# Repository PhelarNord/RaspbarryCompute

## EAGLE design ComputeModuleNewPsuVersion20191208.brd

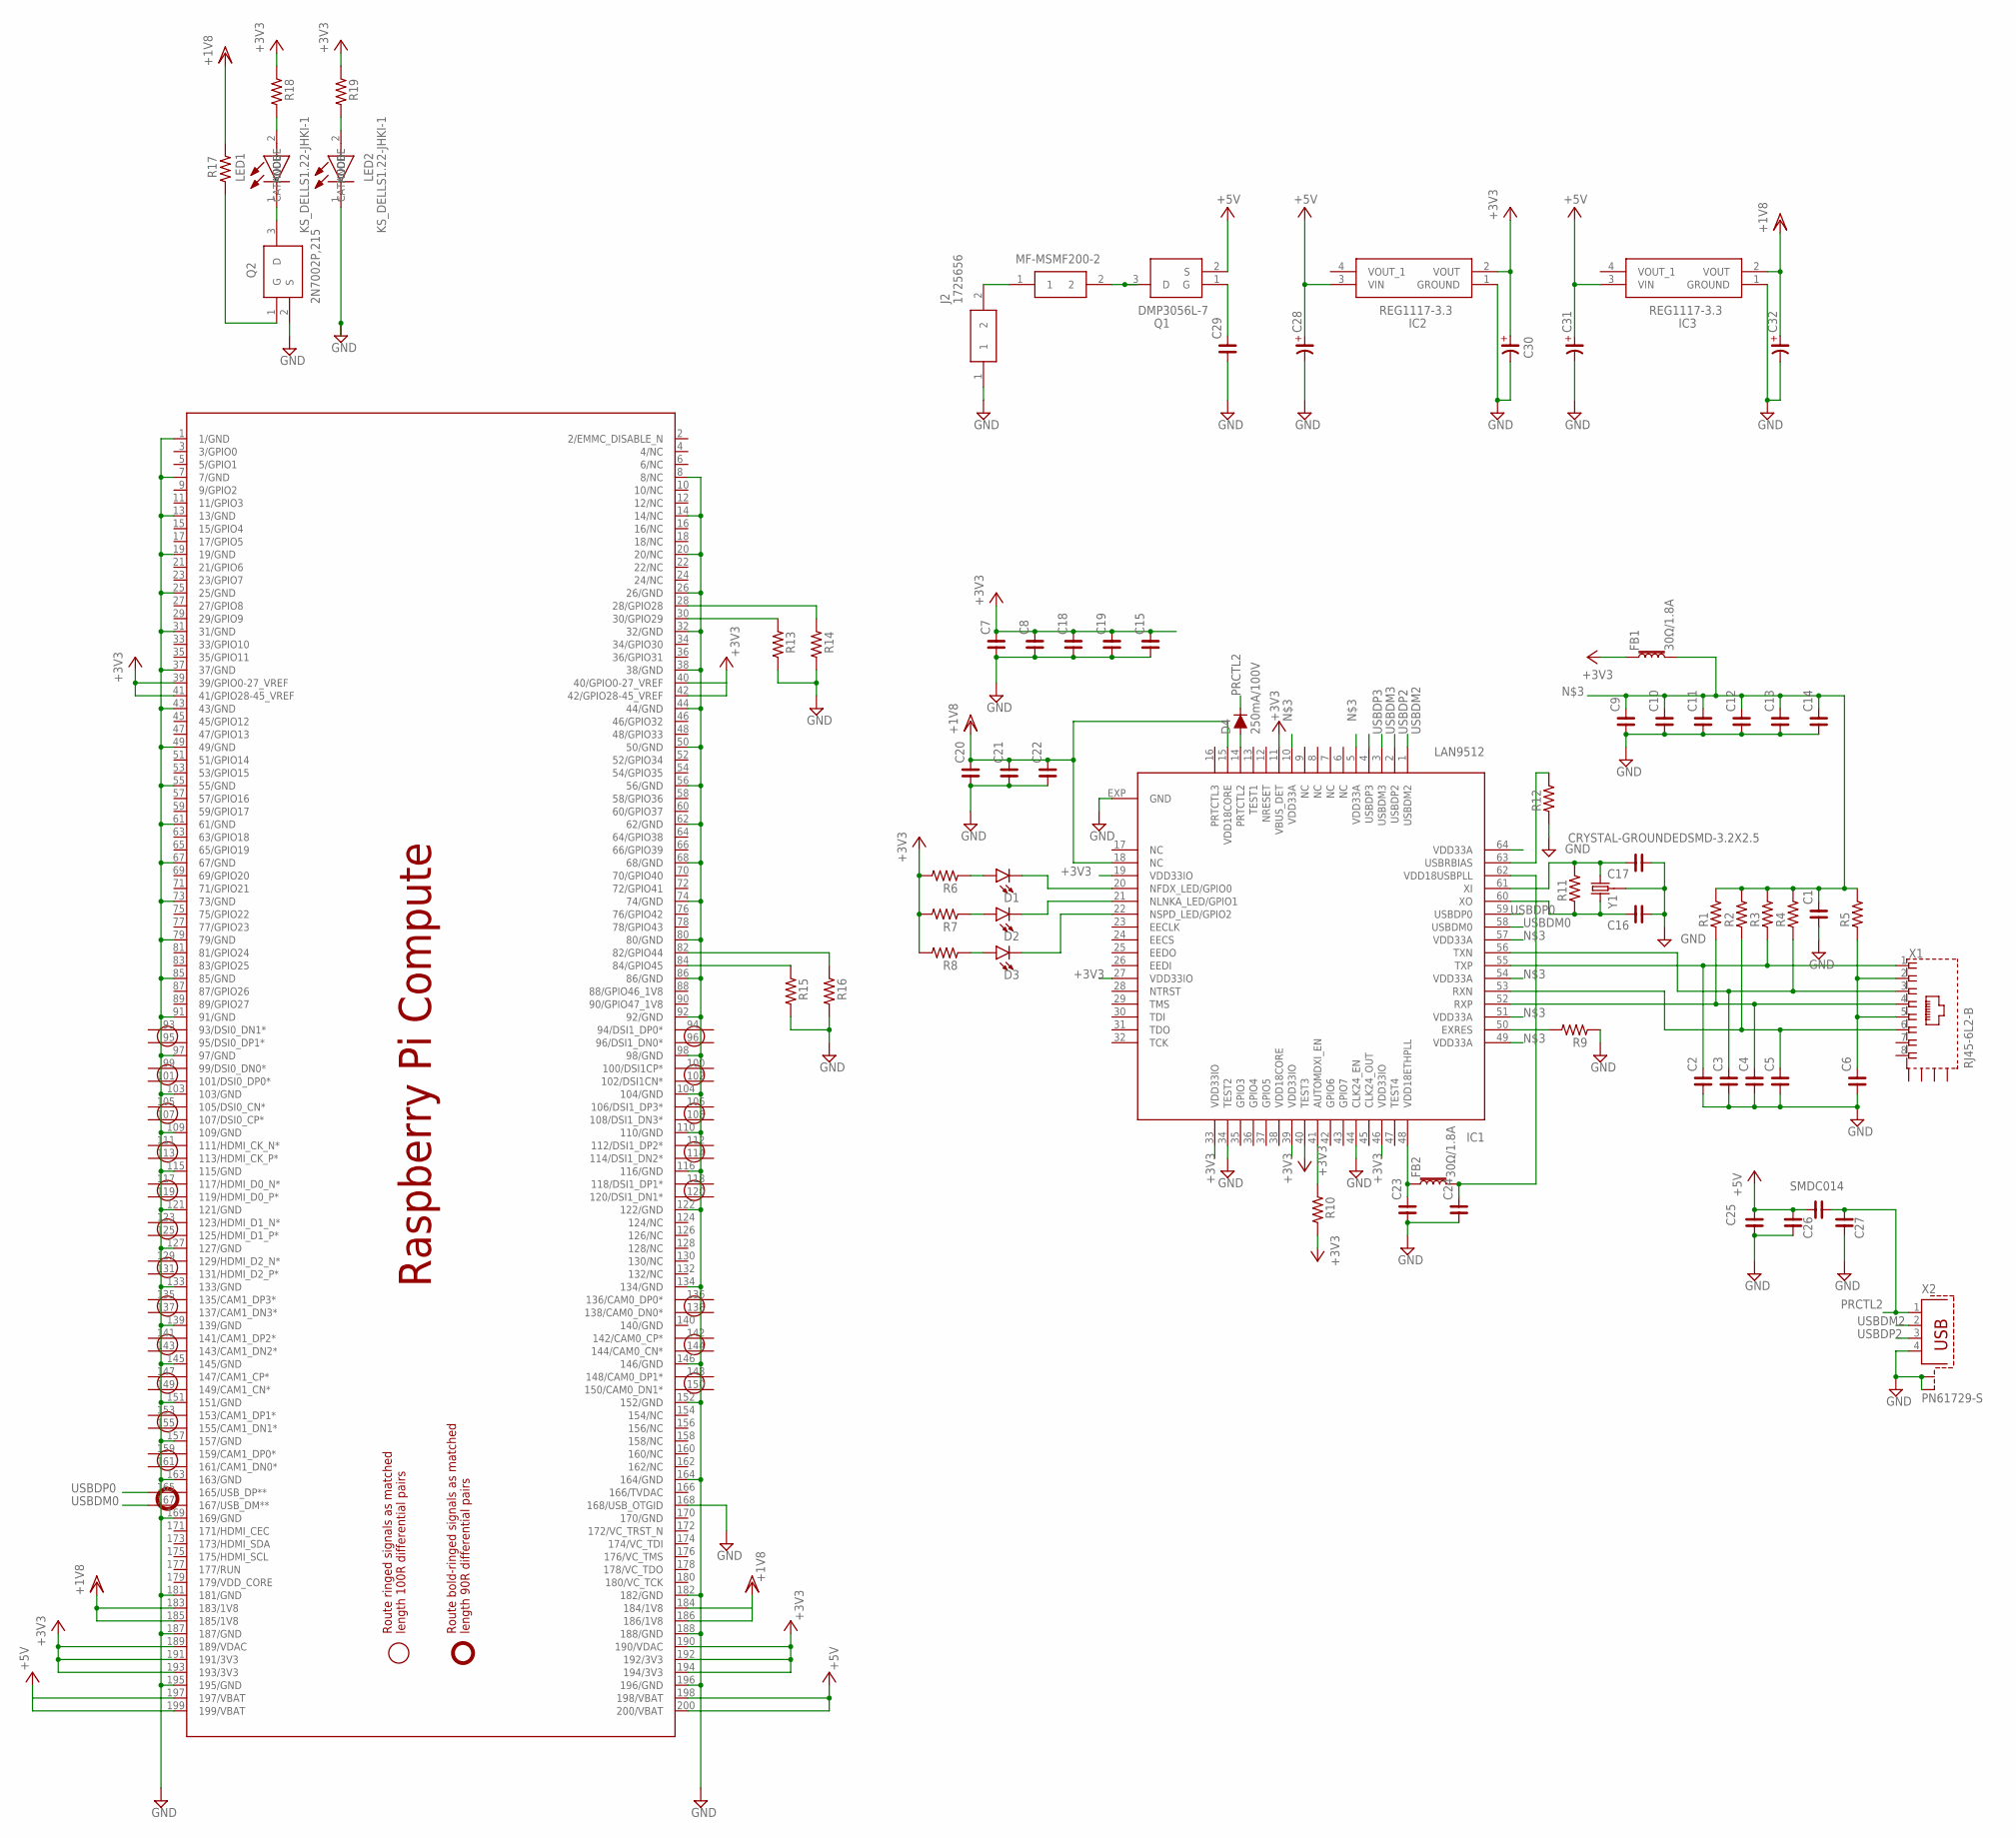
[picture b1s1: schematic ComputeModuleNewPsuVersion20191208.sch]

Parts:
C1, C2, C3, C4, C5, C6, C7, C8, C9, C10, C11, C12, C13, C14, C15, C16, C17, C18, C19, C20, C21, C22, C23, C24, C25, C26, C27, C29: C_0603; C0603
C28, C30, C31, C32: CP_SV-B; CSV-B
D1, D2, D3: LED-FKIT-1206; FKIT-LED-1206
D4: 250mA/100V; SOD-323
F2: MF-MSMF200-2; FUSC4632X85N
FB1, FB2: 30Ω/1.8A; 0603
IC1: LAN9512; QFN64-9X9
IC2, IC3: REG1117-3.3; SOT230P700X180-4N
J2: 1725656
LED1, LED2: KS_DELLS1.22-JHKI-1; KSDELLS122JHKI1
PCB1: RPI_COMPUTE
Q1: DMP3056L-7; SOT96P240X100-3N
Q2: 2N7002P,215; SOT95P230X110-3N
R1, R2, R3, R4, R5, R6, R7, R8, R9, R10, R11, R12, R13, R14, R15, R16, R17, R18, R19: R_0603; R0603
SMDC014: C_1812; C1812
X1: RJ45-6L2-B; RJ45-SHIELD2
X2: PN61729-S
Y1: CRYSTAL-GROUNDEDSMD-3.2X2.5; CRYSTAL-SMD-3.2X2.5MM

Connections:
+3V3: C7.2, C8.2, C15.2, C18.2, C19.2, C30.+, FB1.1, IC1.11 (VBUS_DET), IC1.19 (VDD33IO), IC1.27 (VDD33IO), IC1.33 (VDD33IO), IC1.39 (VDD33IO), IC1.40 (TEST3), IC1.46 (VDD33IO), IC2.2 (VOUT), PCB1.39 (39/GPIO0-27_VREF), PCB1.41 (41/GPIO28-45_VREF), PCB1.42 (42/GPIO28-45_VREF), PCB1.189 (189/VDAC), PCB1.190 (190/VDAC), PCB1.191 (191/3V3), PCB1.192 (192/3V3), PCB1.193 (193/3V3), PCB1.194 (194/3V3), R6.2, R7.2, R8.2, R10.2, R18.1, R19.1
+5V: C25.2, C26.2, C28.+, C31.+, IC2.3 (VIN), IC3.3 (VIN), PCB1.198 (198/VBAT), PCB1.199 (199/VBAT), PCB1.200 (200/VBAT), Q1.2 (S), SMDC014.1
GND: C1.1, C2.1, C3.1, C4.1, C5.1, C6.1, C7.1, C8.1, C9.1, C10.1, C11.1, C12.1, C13.1, C14.1, C15.1, C16.1, C17.1, C18.1, C19.1, C20.1, C21.1, C22.1, C23.1, C24.1, C25.1, C26.1, C27.1, C28.-, C29.1, C30.-, C31.-, C32.-, IC1.34 (TEST2), IC1.44 (CLK24_EN), IC1.EXP (GND), IC2.1 (GROUND), IC3.1 (GROUND), J2.1, LED2.1 (ANODE), PCB1.1 (1/GND), PCB1.7 (7/GND), PCB1.8 (8/NC), PCB1.13 (13/GND), PCB1.14 (14/NC), PCB1.19 (19/GND), PCB1.20 (20/NC), PCB1.25 (25/GND), PCB1.26 (26/GND), PCB1.31 (31/GND), PCB1.32 (32/GND), PCB1.37 (37/GND), PCB1.38 (38/GND), PCB1.43 (43/GND), PCB1.44 (44/GND), PCB1.49 (49/GND), PCB1.50 (50/GND), PCB1.55 (55/GND), PCB1.56 (56/GND), PCB1.61 (61/GND), PCB1.62 (62/GND), PCB1.67 (67/GND), PCB1.68 (68/GND), PCB1.73 (73/GND), PCB1.74 (74/GND), PCB1.79 (79/GND), PCB1.80 (80/GND), PCB1.85 (85/GND), PCB1.86 (86/GND), PCB1.91 (91/GND), PCB1.92 (92/GND), PCB1.97 (97/GND), PCB1.98 (98/GND), PCB1.103 (103/GND), PCB1.104 (104/GND), PCB1.109 (109/GND), PCB1.110 (110/GND), PCB1.115 (115/GND), PCB1.116 (116/GND), PCB1.121 (121/GND), PCB1.122 (122/GND), PCB1.127 (127/GND), PCB1.133 (133/GND), PCB1.134 (134/GND), PCB1.139 (139/GND), PCB1.145 (145/GND), PCB1.146 (146/GND), PCB1.151 (151/GND), PCB1.152 (152/GND), PCB1.157 (157/GND), PCB1.163 (163/GND), PCB1.164 (164/GND), PCB1.168 (168/USB_OTGID), PCB1.169 (169/GND), PCB1.181 (181/GND), PCB1.182 (182/GND), PCB1.187 (187/GND), PCB1.188 (188/GND), PCB1.195 (195/GND), PCB1.196 (196/GND), Q2.2 (S), R9.1, R12.1, R13.2, R14.2, R15.2, R16.2, X2.4, X2.S1, X2.S2, Y1.2 (3), Y1.4 (3)
unnamed: C6.2, R5.1, X1.2, X1.5
unnamed: C2.2, IC1.55 (TXP), R3.1, X1.1
unnamed: C1.2, C9.2, C10.2, C11.2, C12.2, C13.2, C14.2, FB1.2, IC1.5 (VDD33A), IC1.10 (VDD33A), IC1.49 (VDD33A), IC1.51 (VDD33A), IC1.54 (VDD33A), IC1.57 (VDD33A), R1.2, R2.2, R3.2, R4.2, R5.2
unnamed: C3.2, IC1.56 (TXN), R4.1, X1.3
unnamed: C4.2, IC1.52 (RXP), R1.1, X1.4
unnamed: C5.2, IC1.53 (RXN), R2.1, X1.6
unnamed: D1.C, IC1.20 (NFDX_LED/GPIO0)
unnamed: D2.C, IC1.21 (NLNKA_LED/GPIO1)
unnamed: D3.C, IC1.22 (NSPD_LED/GPIO2)
unnamed: D1.A, R6.1
unnamed: D2.A, R7.1
unnamed: D3.A, R8.1
unnamed: IC1.50 (EXRES), R9.2
unnamed: C16.2, IC1.60 (XO), R11.1, Y1.1
unnamed: IC1.41 (AUTOMDXI_EN), R10.1
unnamed: C17.2, IC1.61 (XI), R11.2, Y1.3 (2)
unnamed: C23.2, FB2.1, IC1.48 (VDD18ETHPLL)
unnamed: C24.2, FB2.2, IC1.62 (VDD18USBPLL)
unnamed: LED1.2 (CATHODE), R18.2
unnamed: IC1.63 (USBRBIAS), R12.2
unnamed: D4.A, IC1.14 (PRTCTL2)
unnamed: PCB1.28 (28/GPIO28), R14.1
unnamed: PCB1.30 (30/GPIO29), R13.1
unnamed: PCB1.82 (82/GPIO44), R16.1
unnamed: PCB1.84 (84/GPIO45), R15.1
unnamed: F2.1, J2.2
unnamed: F2.2, Q1.3 (D)
unnamed: C29.2, Q1.1 (G)
unnamed: LED1.1 (ANODE), Q2.3 (D)
unnamed: Q2.1 (G), R17.2
unnamed: LED2.2 (CATHODE), R19.2
PRCTL2: C27.2, D4.C, SMDC014.2, X2.1
USBDM0: IC1.58 (USBDM0), PCB1.167 (167/USB_DM**)
USBDM2: IC1.1 (USBDM2), X2.2
USBDM3: IC1.3 (USBDM3)
USBDP0: IC1.59 (USBDP0), PCB1.165 (165/USB_DP**)
USBDP2: IC1.2 (USBDP2), X2.3
USBDP3: IC1.4 (USBDP3)
VDD: C20.2, C21.2, C22.2, C32.+, IC1.15 (VDD18CORE), IC1.18 (NC), IC3.2 (VOUT), PCB1.183 (183/1V8), PCB1.185 (185/1V8), PCB1.186 (186/1V8), R17.1

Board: 2 copper layers, 71 parts (0 on the bottom side), 40 nets, no tracks yet.

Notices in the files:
parts and their libraries:
rc-master-smd: Copyright (C) 2007, Bob Starr
SparkFun-Coils: Licensing: Creative Commons ShareAlike 4.0 International - https://creativecommons.org/licenses/by-sa/4.0
